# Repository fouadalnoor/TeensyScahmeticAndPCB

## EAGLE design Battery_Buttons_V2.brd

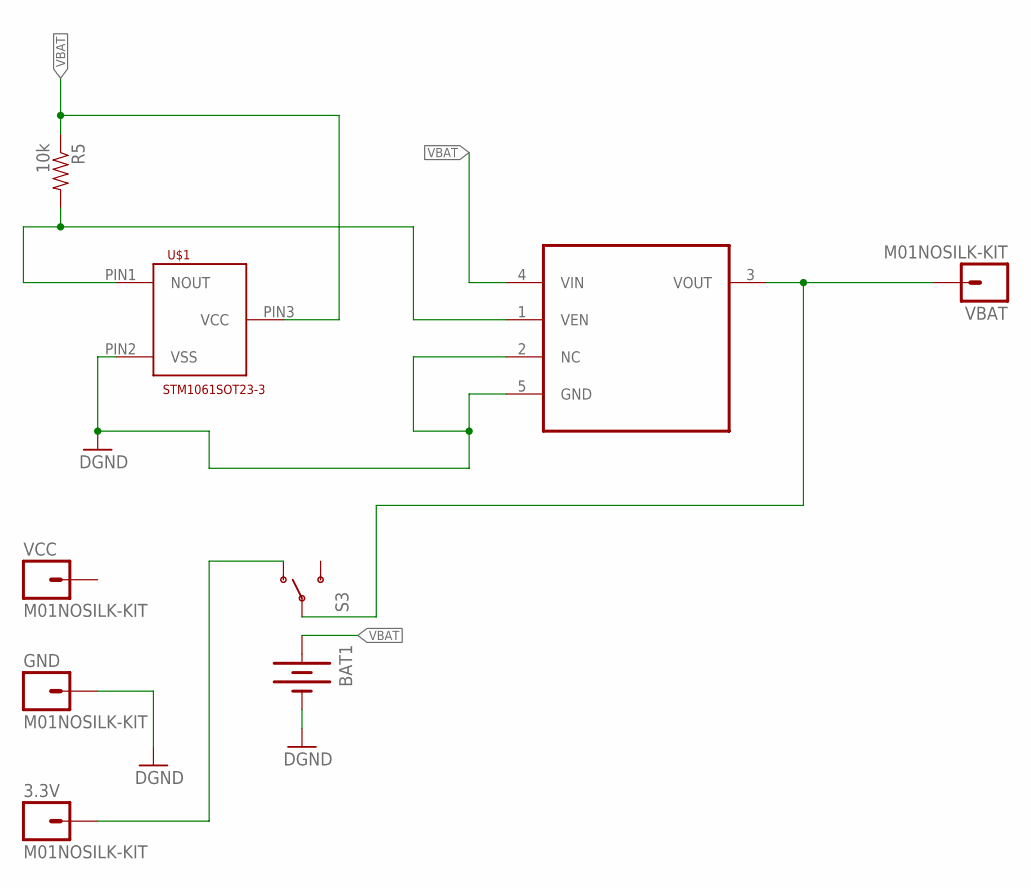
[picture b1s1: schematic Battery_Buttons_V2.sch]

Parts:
3.3V: M01NOSILK-KIT; 1X01NS-KIT
BAT1: BATTERY245PTH; BATTCON_245MM_PTH
GND: M01NOSILK-KIT; 1X01NS-KIT
R5: 10k; 0603-RES
S3: SWITCH-SPDT-SMD-A; SWITCH-SPST-SMD-A
U4: LP38693MP-3.3; SOT150P696X180-5N
U$1: STM1061SOT23-3; STM1061
VBAT: M01NOSILK-KIT; 1X01NS-KIT
VCC: M01NOSILK-KIT; 1X01NS-KIT

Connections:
DGND: BAT1.GND (-)
GND: GND.1, U4.2 (NC), U4.5 (GND), U$1.PIN2 (VSS)
unnamed: S3.2, U4.3 (VOUT), VBAT.1
unnamed: R5.2, U4.1 (VEN), U$1.PIN1 (NOUT)
unnamed: 3.3V.1, S3.1 (O)
unnamed: R5.1, U$1.PIN3 (VCC)
VBAT: BAT1.POS1 (+), BAT1.POS2 (+)

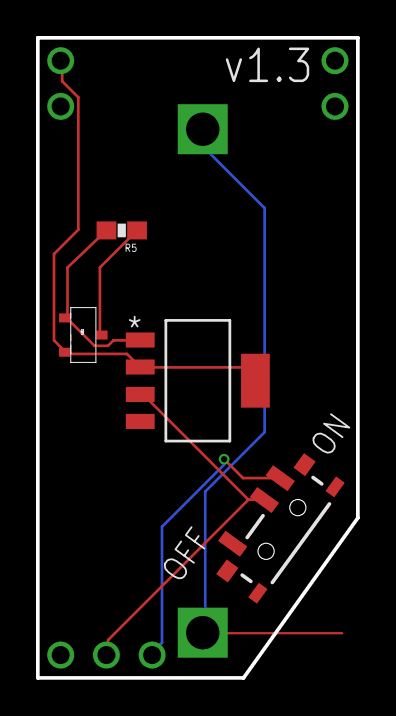
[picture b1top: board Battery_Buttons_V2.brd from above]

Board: 2 copper layers, 17.8 x 35.6 mm, 9 parts (1 on the bottom side), 6 nets.

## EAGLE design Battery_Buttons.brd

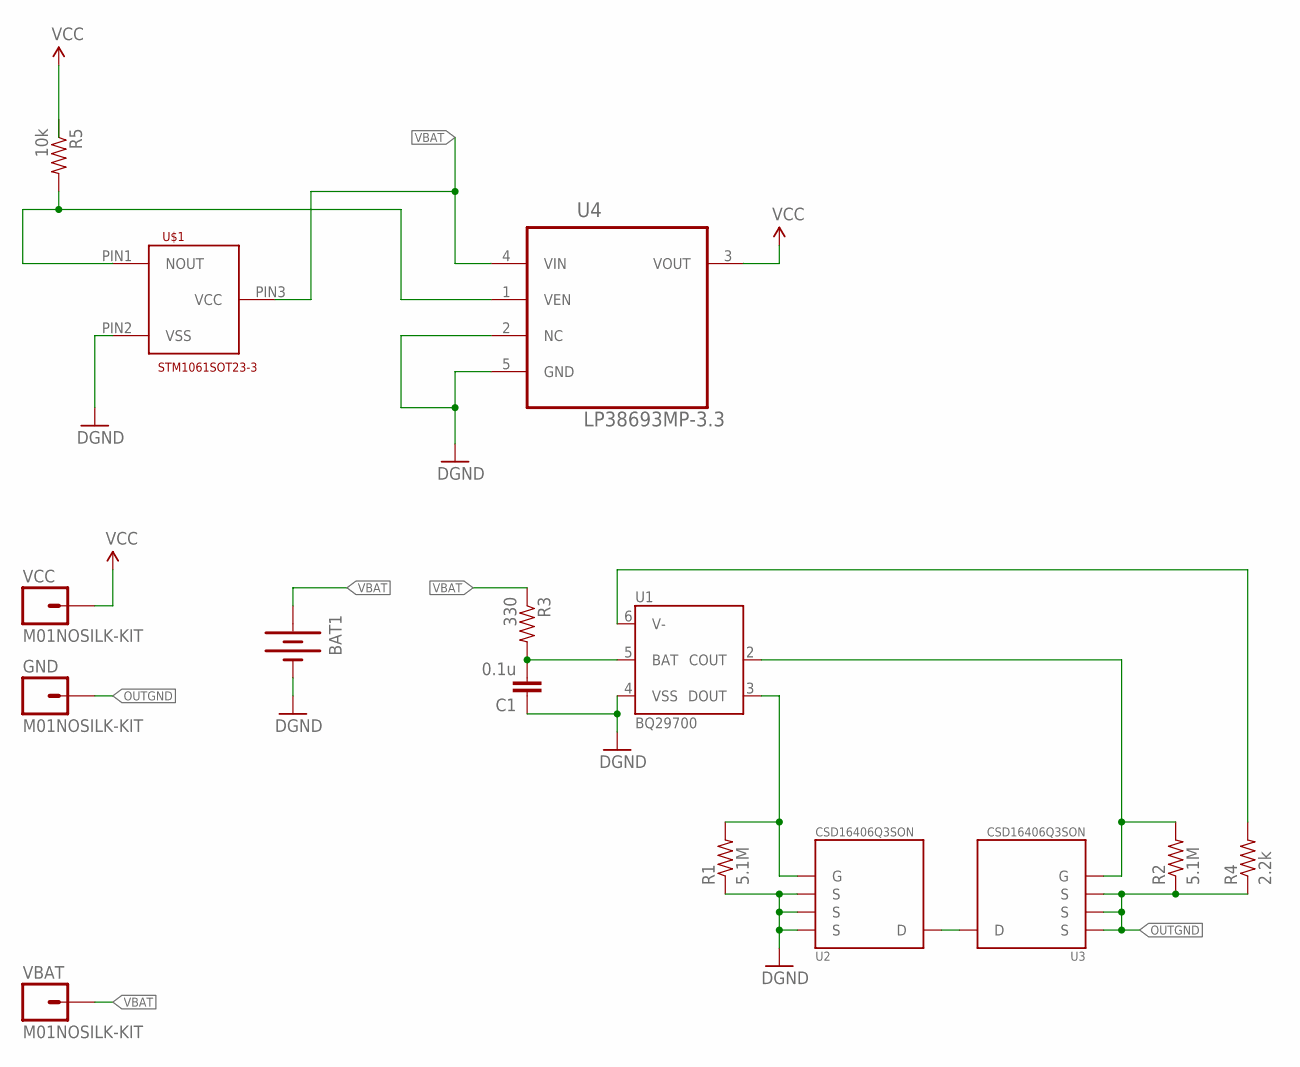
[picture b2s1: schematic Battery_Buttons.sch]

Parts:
BAT1: BATTERY245PTH; BATTCON_245MM_PTH
C1: 0.1u; 0603-CAP
GND: M01NOSILK-KIT; 1X01NS-KIT
R1, R2: 5.1M; 0603-RES
R3: 330; 0603-RES
R4: 2.2k; 0603-RES
R5: 10k; 0603-RES
U1: BQ29700; WSON(6)
U2, U3: CSD16406Q3SON; SON(330X330)
U4: LP38693MP-3.3; SOT150P696X180-5N
U$1: STM1061SOT23-3; STM1061
VBAT: M01NOSILK-KIT; 1X01NS-KIT
VCC: M01NOSILK-KIT; 1X01NS-KIT

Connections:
DGND: BAT1.GND (-), C1.1, R1.1, U1.4 (VSS), U2.1 (S), U2.2 (S), U2.3 (S)
GND: U4.2 (NC), U4.5 (GND), U$1.PIN2 (VSS)
unnamed: U2.5 (D), U3.5 (D)
unnamed: C1.2, R3.2, U1.5 (BAT)
unnamed: R5.2, U4.1 (VEN), U$1.PIN1 (NOUT)
unnamed: R1.2, U1.3 (DOUT), U2.4 (G)
unnamed: R2.2, U1.2 (COUT), U3.4 (G)
unnamed: R4.2, U1.6 (V-)
unnamed: U4.4 (VIN), U$1.PIN3 (VCC)
OUTGND: GND.1, R2.1, R4.1, U3.1 (S), U3.2 (S), U3.3 (S)
VBAT: BAT1.POS1 (+), BAT1.POS2 (+), R3.1, VBAT.1
VCC: U4.3 (VOUT), VCC.1

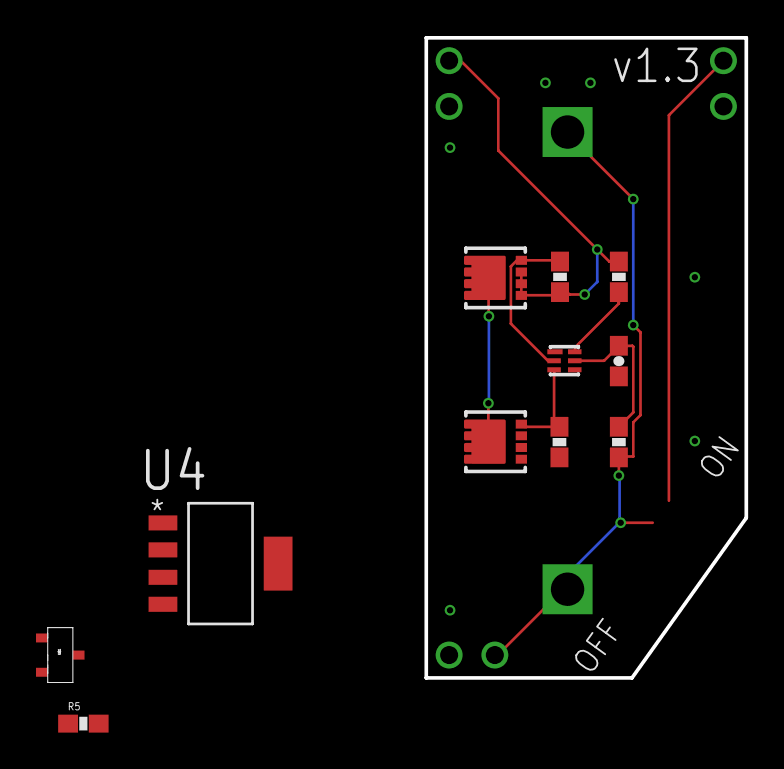
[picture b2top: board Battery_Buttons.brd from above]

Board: 2 copper layers, 17.8 x 35.6 mm, 15 parts (1 on the bottom side), 12 nets.

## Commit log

2016-06-14 Added Eagle files
2016-06-15 created new Battery package and added it to the PCB. I have also moved the switch around. Need to check for DRC errors etc

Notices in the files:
parts and their libraries:
SparkFun-Electromechanical: Licensing: Creative Commons ShareAlike 4.0 International - https://creativecommons.org/licenses/by-sa/4.0
